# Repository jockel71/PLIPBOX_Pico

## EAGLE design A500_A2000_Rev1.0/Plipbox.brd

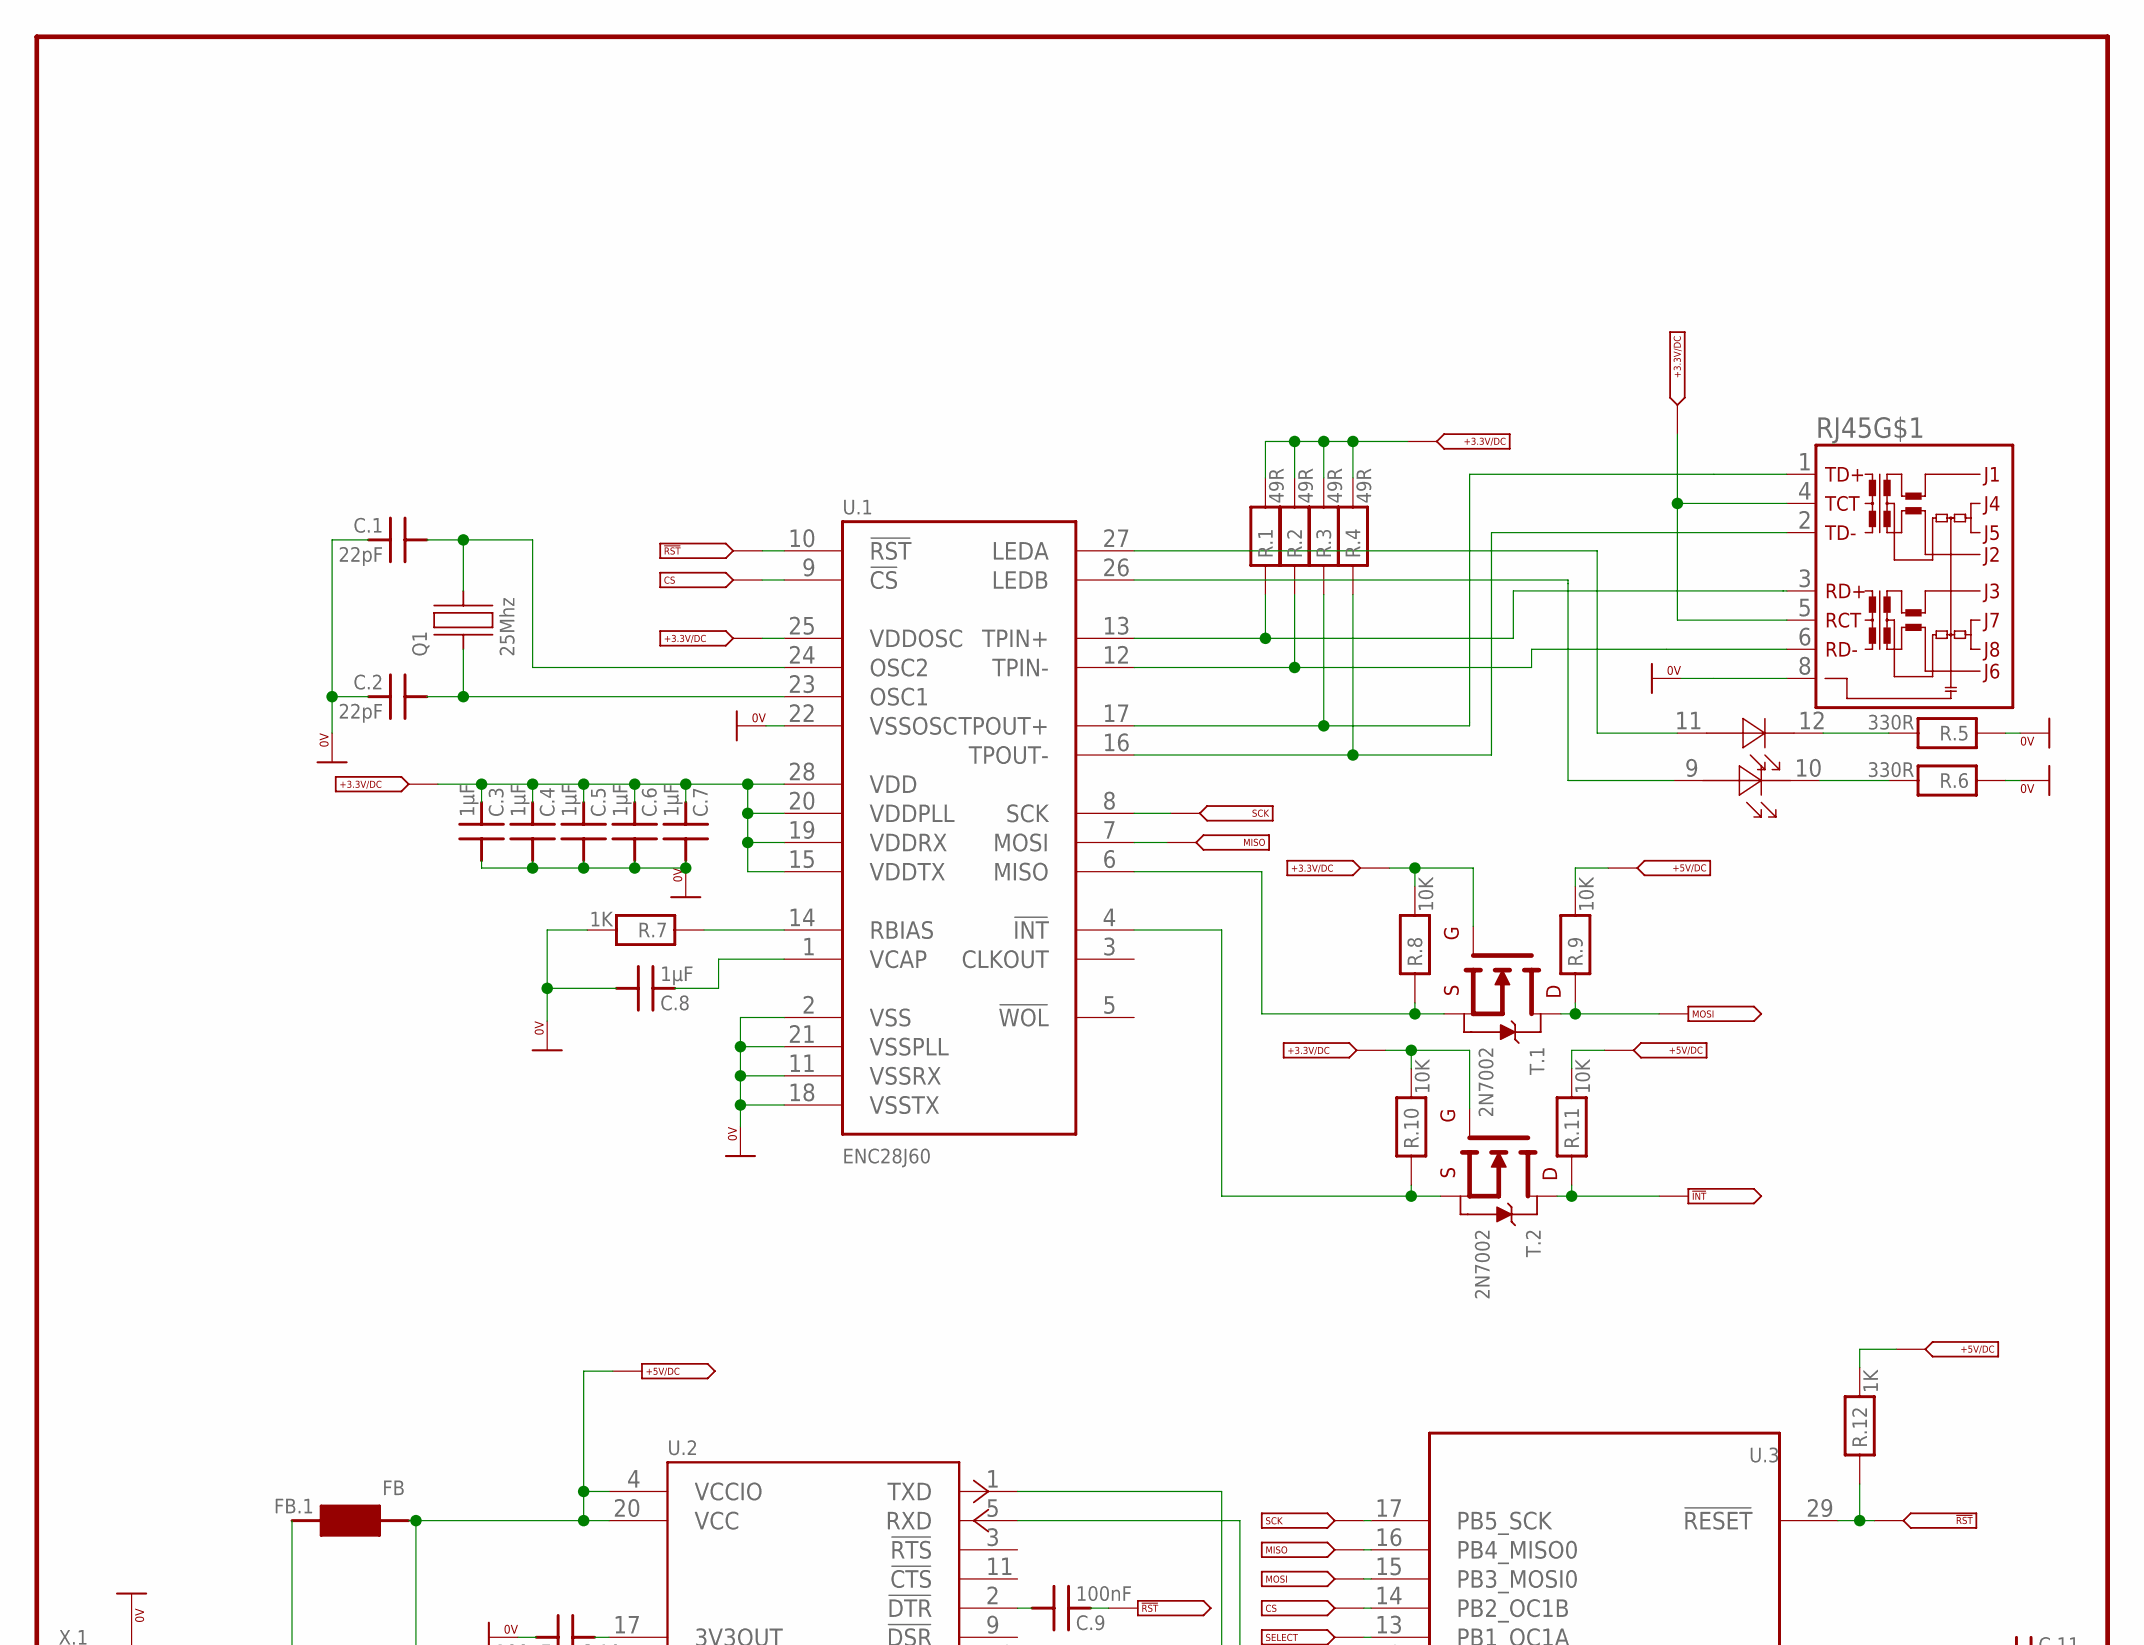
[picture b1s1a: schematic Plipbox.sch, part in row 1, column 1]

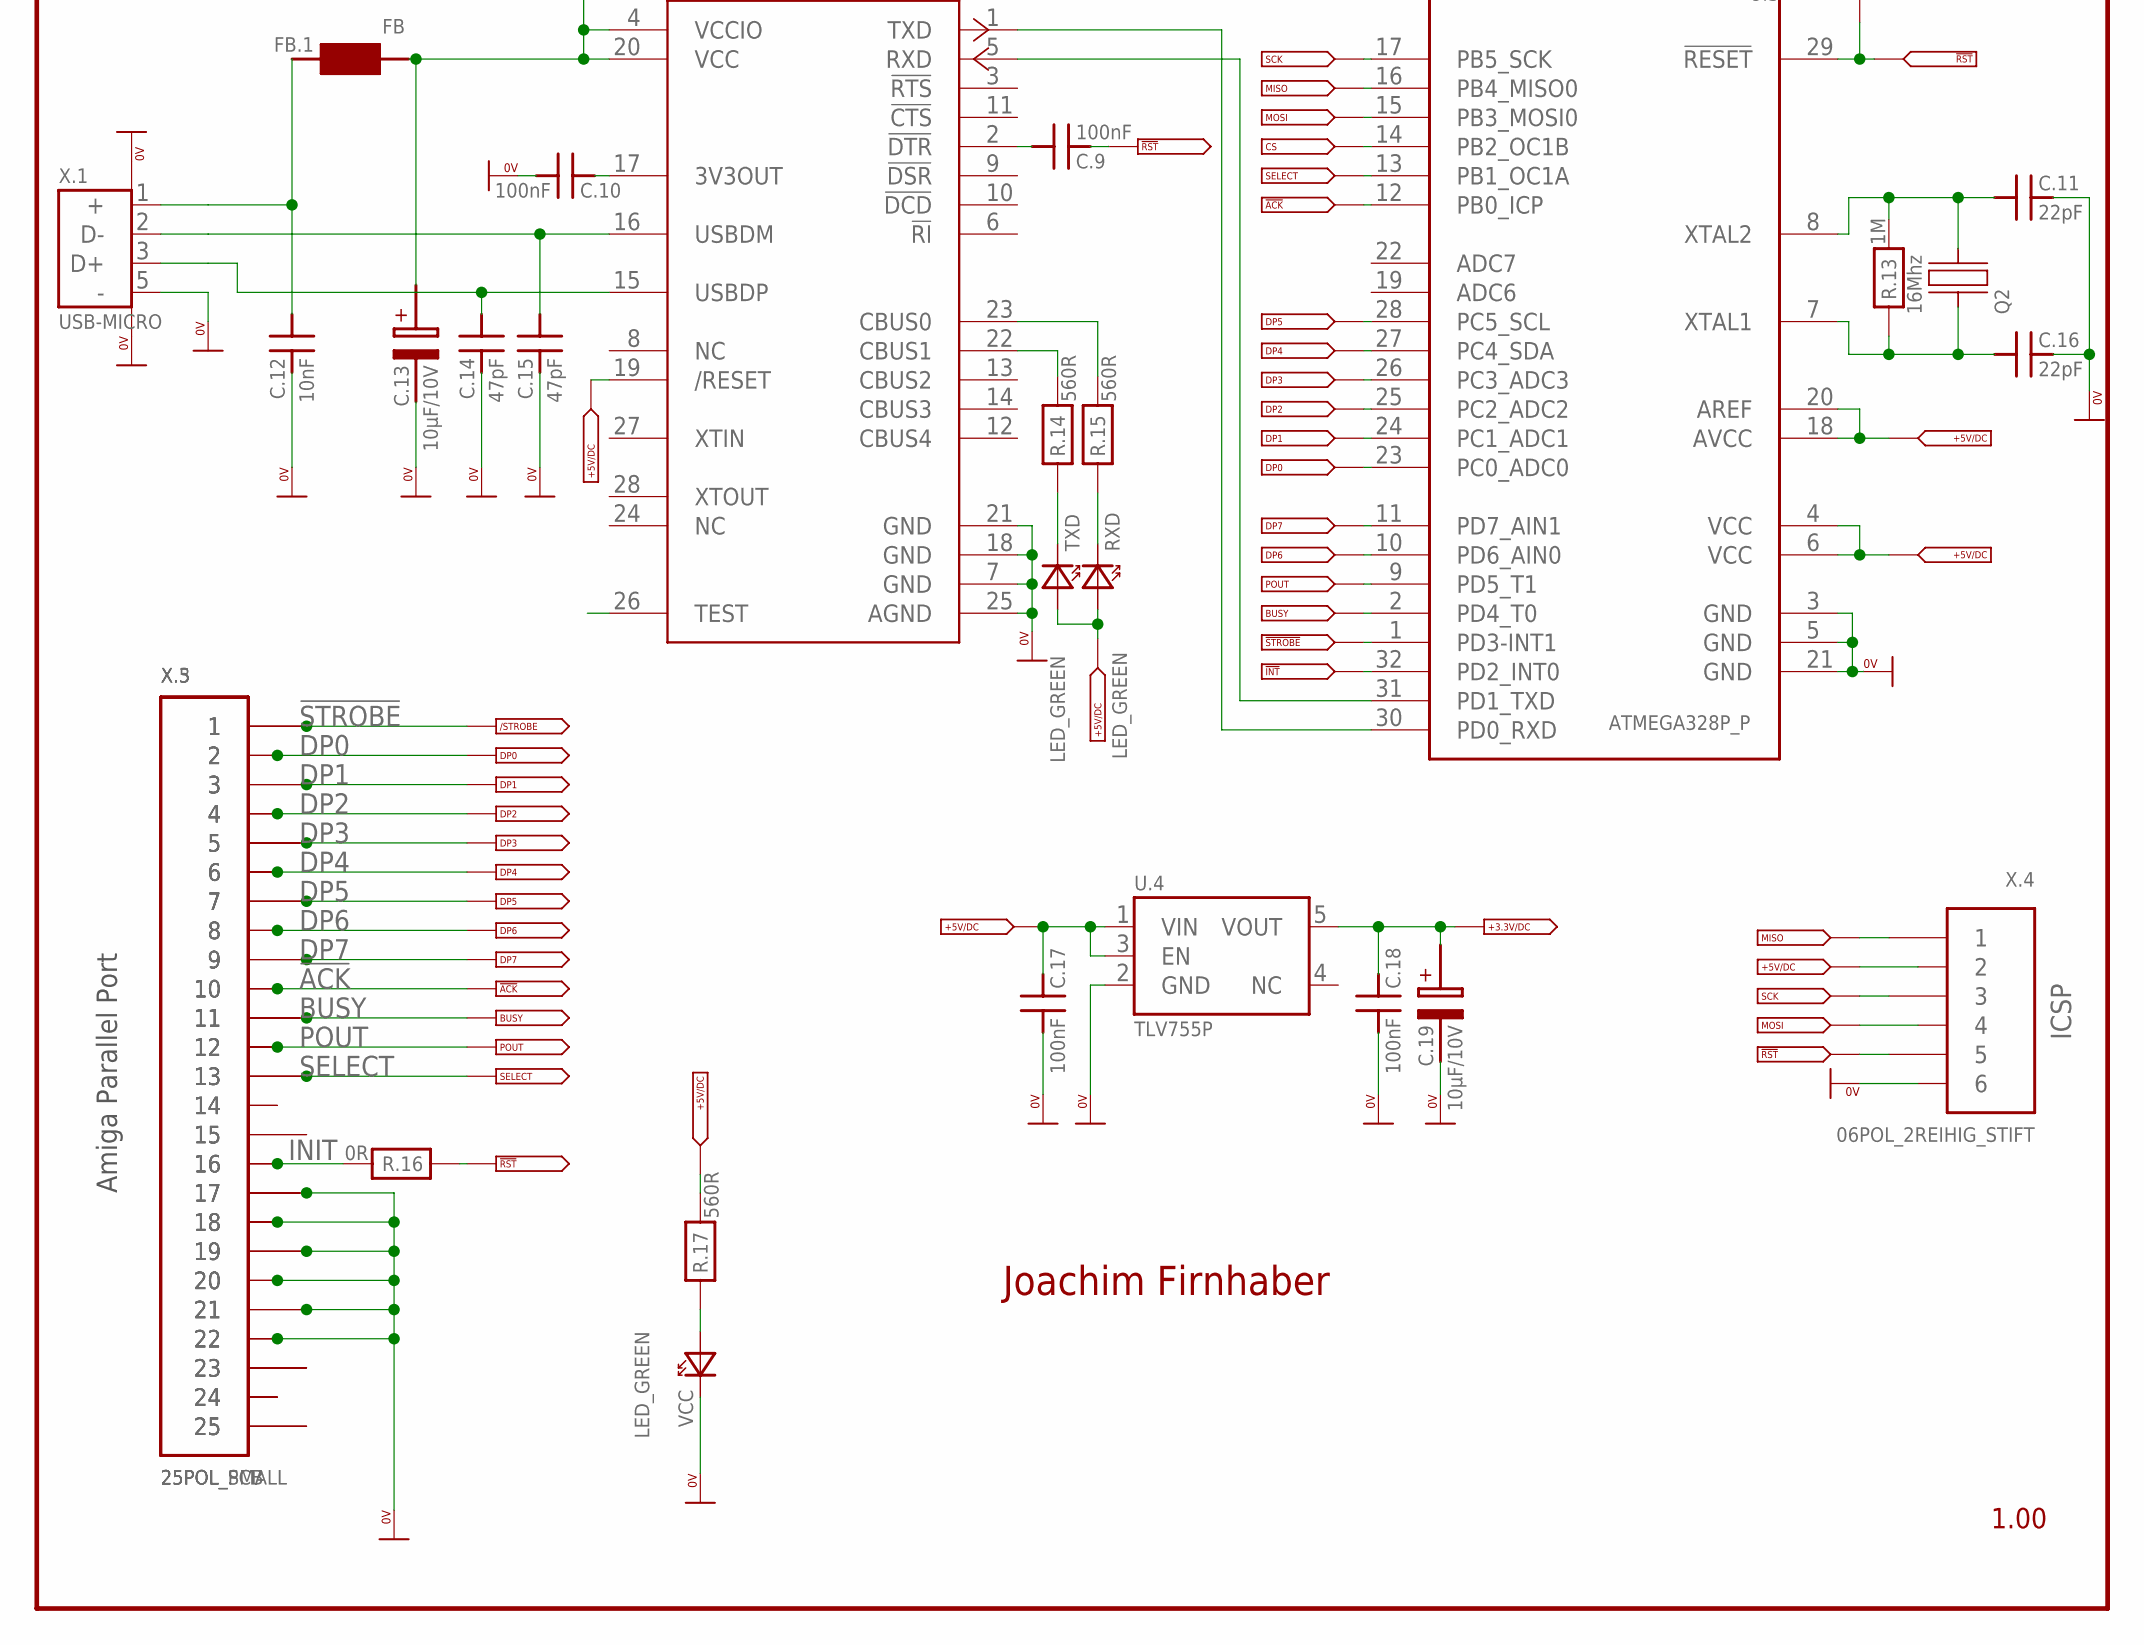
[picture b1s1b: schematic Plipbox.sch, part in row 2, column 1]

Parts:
C.1, C.2, C.11, C.16: 22pF; 0805
C.3, C.4, C.5, C.6, C.7, C.8: 1µF; 0805
C.9, C.10, C.17, C.18: 100nF; 0805
C.12: 10nF; 0805
C.13, C.19: 10µF/10V; 3216
C.14, C.15: 47pF; 0805
FB.1: FB; 0805
Q1: 25Mhz; 3,4X2,7X0,75
Q2: 16Mhz; 3,4X2,7X0,75
R.1, R.2, R.3, R.4: 49R; 0805
R.5, R.6: 330R; 0805
R.7, R.12: 1K; 0805
R.8, R.9, R.10, R.11: 10K; 0805
R.13: 1M; 0805
R.14, R.15, R.17: 560R; 0805
R.16: 0R; 0805
RJ45: WE-RJ45_LAN_7499011222; WE-RJ45_LAN_10/100_BASET_7499011222
RXD: LED_GREEN; 0805
T.1, T.2: 2N7002; SOT23
TXD: LED_GREEN; 0805
U.1: ENC28J60; SSOP28
U.2: FT232R_FT232RL; SSOP28
U.3: ATMEGA328P_P; LQFP32
U.4: TLV755P; SOT23-5
VCC: LED_GREEN; 0805
X.1: USB-MICRO; USB_MICRO
X.3: 25POL_SMALL; SUB-D_25_M_ONLY
X.4: 06POL_2REIHIG_STIFT; STIFT_2*03
X.5: 25POL_PCB; SUB-D_25M_L

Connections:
0V: C.1.2, C.2.2, C.3.1, C.4.1, C.5.1, C.6.1, C.7.1, C.8.1, C.10.1, C.11.2, C.12.2, C.13.-, C.14.2, C.15.2, C.16.2, C.17.1, C.18.1, C.19.-, R.5.1, R.6.1, R.7.2, RJ45.8, U.1.2 (VSS), U.1.11 (VSSRX), U.1.18 (VSSTX), U.1.21 (VSSPLL), U.1.22 (VSSOSC), U.2.7 (GND), U.2.18 (GND), U.2.21 (GND), U.2.25 (AGND), U.3.3 (GND), U.3.5 (GND), U.3.21 (GND), U.4.2 (GND), VCC.K (KATHODE), X.1.5 (-), X.1.6 (GND), X.1.7 (GND), X.3.17, X.3.18, X.3.19, X.3.20, X.3.21, X.3.22, X.4.6, X.5.17, X.5.18, X.5.19, X.5.20, X.5.21, X.5.22
!ACK: U.3.12 (PB0_ICP), X.3.10, X.5.10
!INT: R.11.1, T.2.3 (DRAIN), U.3.32 (PD2_INT0)
!RST: C.9.2, R.12.1, R.16.1, U.1.10 (!RST), U.3.29 (!RESET), X.4.5
!STROBE: U.3.1 (PD3-INT1), X.3.1, X.5.1
+3.3V: C.3.2, C.4.2, C.5.2, C.6.2, C.7.2, C.18.2, C.19.+, R.1.2, R.2.2, R.3.2, R.4.2, R.8.2, R.10.2, RJ45.4, RJ45.5, T.1.1 (GATE), T.2.1 (GATE), U.1.15 (VDDTX), U.1.19 (VDDRX), U.1.20 (VDDPLL), U.1.25 (VDDOSC), U.1.28 (VDD), U.4.5 (VOUT)
+5V: C.13.+, C.17.2, FB.1.1, R.9.2, R.11.2, R.12.2, R.17.2, RXD.A (ANODE), TXD.A (ANODE), U.2.4 (VCCIO), U.2.19 (/RESET), U.2.20 (VCC), U.3.4 (VCC), U.3.6 (VCC), U.3.18 (AVCC), U.3.20 (AREF), U.4.1 (VIN), U.4.3 (EN), X.4.2
/RXLED: R.14.2, U.2.22 (CBUS1)
/TXLED: R.15.2, U.2.23 (CBUS0)
BUSY: U.3.2 (PD4_T0), X.3.11, X.5.11
CS: U.1.9 (!CS), U.3.14 (PB2_OC1B)
DP0: U.3.23 (PC0_ADC0), X.3.2, X.5.2
DP1: U.3.24 (PC1_ADC1), X.3.3, X.5.3
DP2: U.3.25 (PC2_ADC2), X.3.4, X.5.4
DP3: U.3.26 (PC3_ADC3), X.3.5, X.5.5
DP4: U.3.27 (PC4_SDA), X.3.6, X.5.6
DP5: U.3.28 (PC5_SCL), X.3.7, X.5.7
DP6: U.3.10 (PD6_AIN0), X.3.8, X.5.8
DP7: U.3.11 (PD7_AIN1), X.3.9, X.5.9
INIT: R.16.2, X.3.16, X.5.16
MISO: U.1.7 (MOSI), U.3.16 (PB4_MISO0), X.4.1
MOSI: R.9.1, T.1.3 (DRAIN), U.3.15 (PB3_MOSI0), X.4.4
unnamed: C.16.1, Q2.2 (XTAL1), R.13.1, U.3.7 (XTAL1)
unnamed: R.4.1, RJ45.2, U.1.16 (TPOUT-)
unnamed: C.9.1, U.2.2 (!DTR)
unnamed: R.1.1, RJ45.3, U.1.13 (TPIN+)
unnamed: C.11.1, Q2.4 (XTAL2), R.13.2, U.3.8 (XTAL2)
unnamed: R.2.1, RJ45.6, U.1.12 (TPIN-)
unnamed: R.3.1, RJ45.1, U.1.17 (TPOUT+)
unnamed: C.8.2, U.1.1 (VCAP)
unnamed: R.7.1, U.1.14 (RBIAS)
unnamed: R.8.1, T.1.2 (SOURCE), U.1.6 (MISO)
unnamed: X.3.14, X.5.14
unnamed: C.2.1, Q1.2 (XTAL1), U.1.23 (OSC1)
unnamed: C.1.1, Q1.4 (XTAL2), U.1.24 (OSC2)
unnamed: R.10.1, T.2.2 (SOURCE), U.1.4 (!INT)
unnamed: X.3.15, X.5.15
unnamed: X.3.23, X.5.23
unnamed: X.3.24, X.5.24
unnamed: X.3.25, X.5.25
unnamed: RJ45.11 (A), U.1.27 (LEDA)
unnamed: RJ45.9 (A), U.1.26 (LEDB)
unnamed: R.6.2, RJ45.10 (K)
unnamed: R.5.2, RJ45.12 (K)
unnamed: C.10.2, U.2.17 (3V3OUT)
unnamed: R.15.1, RXD.K (KATHODE)
unnamed: R.14.1, TXD.K (KATHODE)
unnamed: U.2.1 (TXD), U.3.30 (PD0_RXD)
unnamed: R.17.1, VCC.A (ANODE)
unnamed: C.12.1, FB.1.2, X.1.1 (+)
POUT: U.3.9 (PD5_T1), X.3.12, X.5.12
SCK: U.1.8 (SCK), U.3.17 (PB5_SCK), X.4.3
SELECT: U.3.13 (PB1_OC1A), X.3.13, X.5.13
TXD1: U.2.5 (RXD), U.3.31 (PD1_TXD)
USB+: C.14.1, U.2.15 (USBDP), X.1.3 (D+)
USB-: C.15.1, U.2.16 (USBDM), X.1.2 (D-)

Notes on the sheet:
Amiga Parallel Port
ICSP
1.00
Joachim Firnhaber

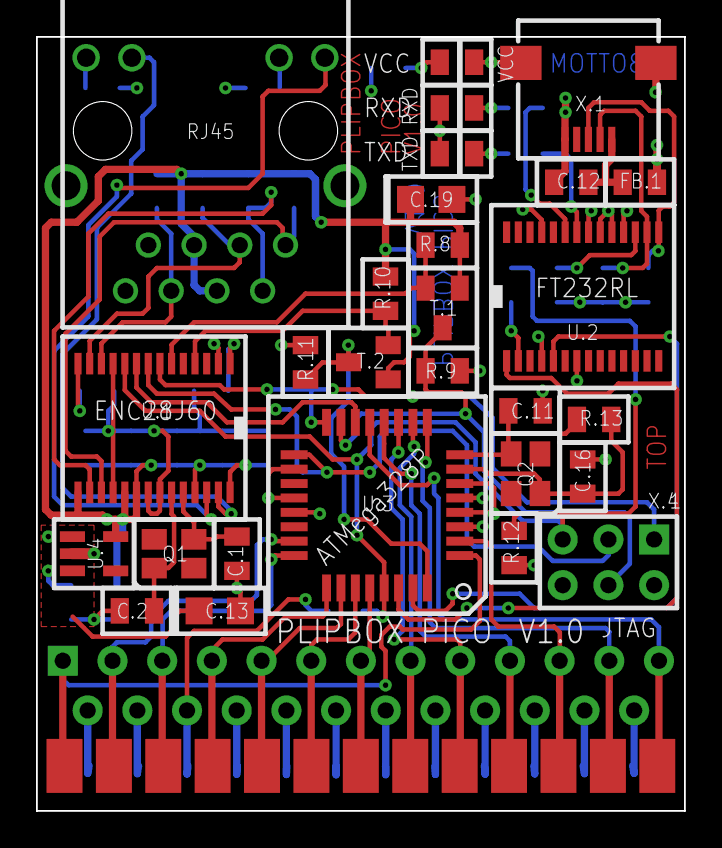
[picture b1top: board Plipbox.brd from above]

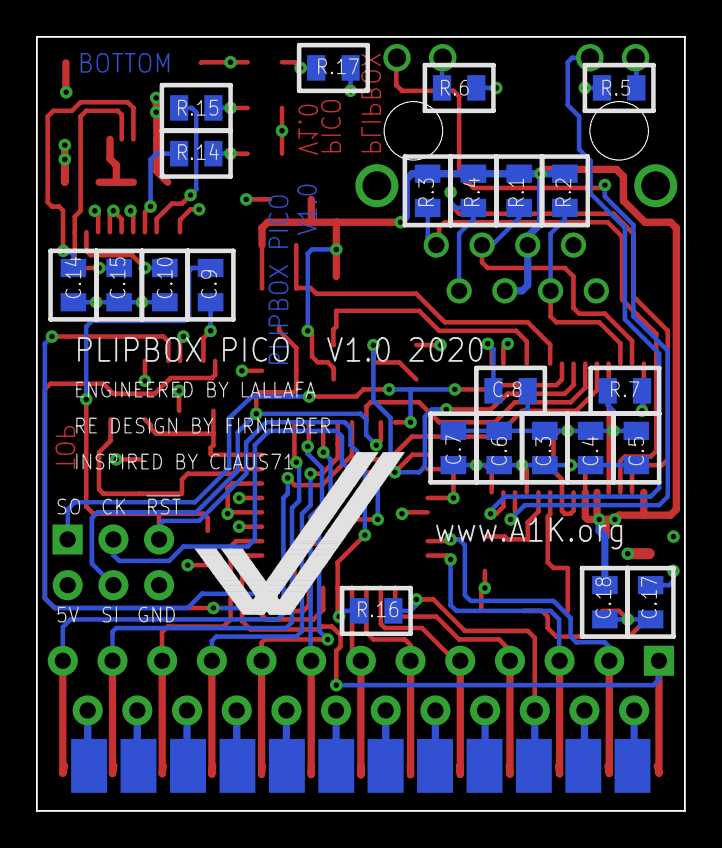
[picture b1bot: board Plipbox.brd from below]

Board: 4 copper layers, 36.0 x 43.0 mm, 53 parts (23 on the bottom side), 56 nets.
